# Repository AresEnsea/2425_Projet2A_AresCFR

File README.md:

# 2425_AresCFR
Ce repository contient le travail de l'association Arès dans le cadre de la Coupe de France de Robotique 2024-2025. Il contient tous les fichiers CAO, Kicad, Python, C ainsi que les photos, diagrammes et schémas qui ont fait avancer le projet.

## Répartition
Dépôt du projet de coupe de France de robotique 2024/2025
- 1A : Ce repository contient le travail des 1ères années membres de l'association Arès à l'ENSEA sur les PAMIs de la Coupe de France de Robotique

Read me 1A :
      https://github.com/AresEnsea/2425_Projet2A_AresCFR/blob/main/1A/README.md
      
- 2A : Ce repository contient le travail des 2èmes années membres de l'association Arès à l'ENSEA sur le robot principal de la Coupe de France de Robotique

Read me 2A :
      https://github.com/AresEnsea/2425_Projet2A_AresCFR/blob/main/2A/README.md

https://github.com/user-attachments/assets/8da76ca9-4337-4687-90c1-276035e22721

## Règlement
Le but de la compétition est de faire réaliser des actions de différentes difficultés grâce à des robots complétement autonomes, en lien avec le thème de l'année. Cette année le robot principal devra pouvoir se déplacer, déplacer des cannettes et des planches en bois de sorte à les empiler selon l'ordre suivant (2 canettes - 1 planche, 2 canettes - 1 planche , 2 canettes - 1 planche) pour un maximum de 3 étages, chaque étage rapporte plus de points que le précédent, le tout pour atteindre le score le plus grand. Cette année les PAMIs (Petits Actionneur Motorisés Indépendants) censés aider le robot principal en rapportant également des points sont d'une grande importance puisque rapporte en théorie autant de points qiue le robot principal, ils réaliseront des actions simples (déplacement et activation d'un actionneurs), un se distingue parmi eux le "Superstar" qui devra grimper sur l'estrade de la table et se rapprocher le plus du bord sans tomber pour gagner des points.

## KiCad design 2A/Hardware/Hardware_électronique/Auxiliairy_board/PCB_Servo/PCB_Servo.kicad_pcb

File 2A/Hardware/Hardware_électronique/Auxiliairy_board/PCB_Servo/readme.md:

# PCB_Servo

## Description :
- Carte servant d'intermédiaire entre la mainboard et tous les servos du robot

## Caractéristiques techniques :
- Le connecteur JST 4 pins recoit la puissance et une information UART de la carte mainboard
- La puissance est convertie en 7.4V pour alimenter les servos
- Le 7.4V est convertie en 3.3V pour alimenter le microprocesseur STM32G071CBUx
- L'information UART est traduite par le microprocesseur en un signal PWM par servo

# Issues
- le modèle de servo moteur devant etre utilisé à changé après avoir finis le routage, il a fallu alors reprendre le routage de toute la puissance de la carte

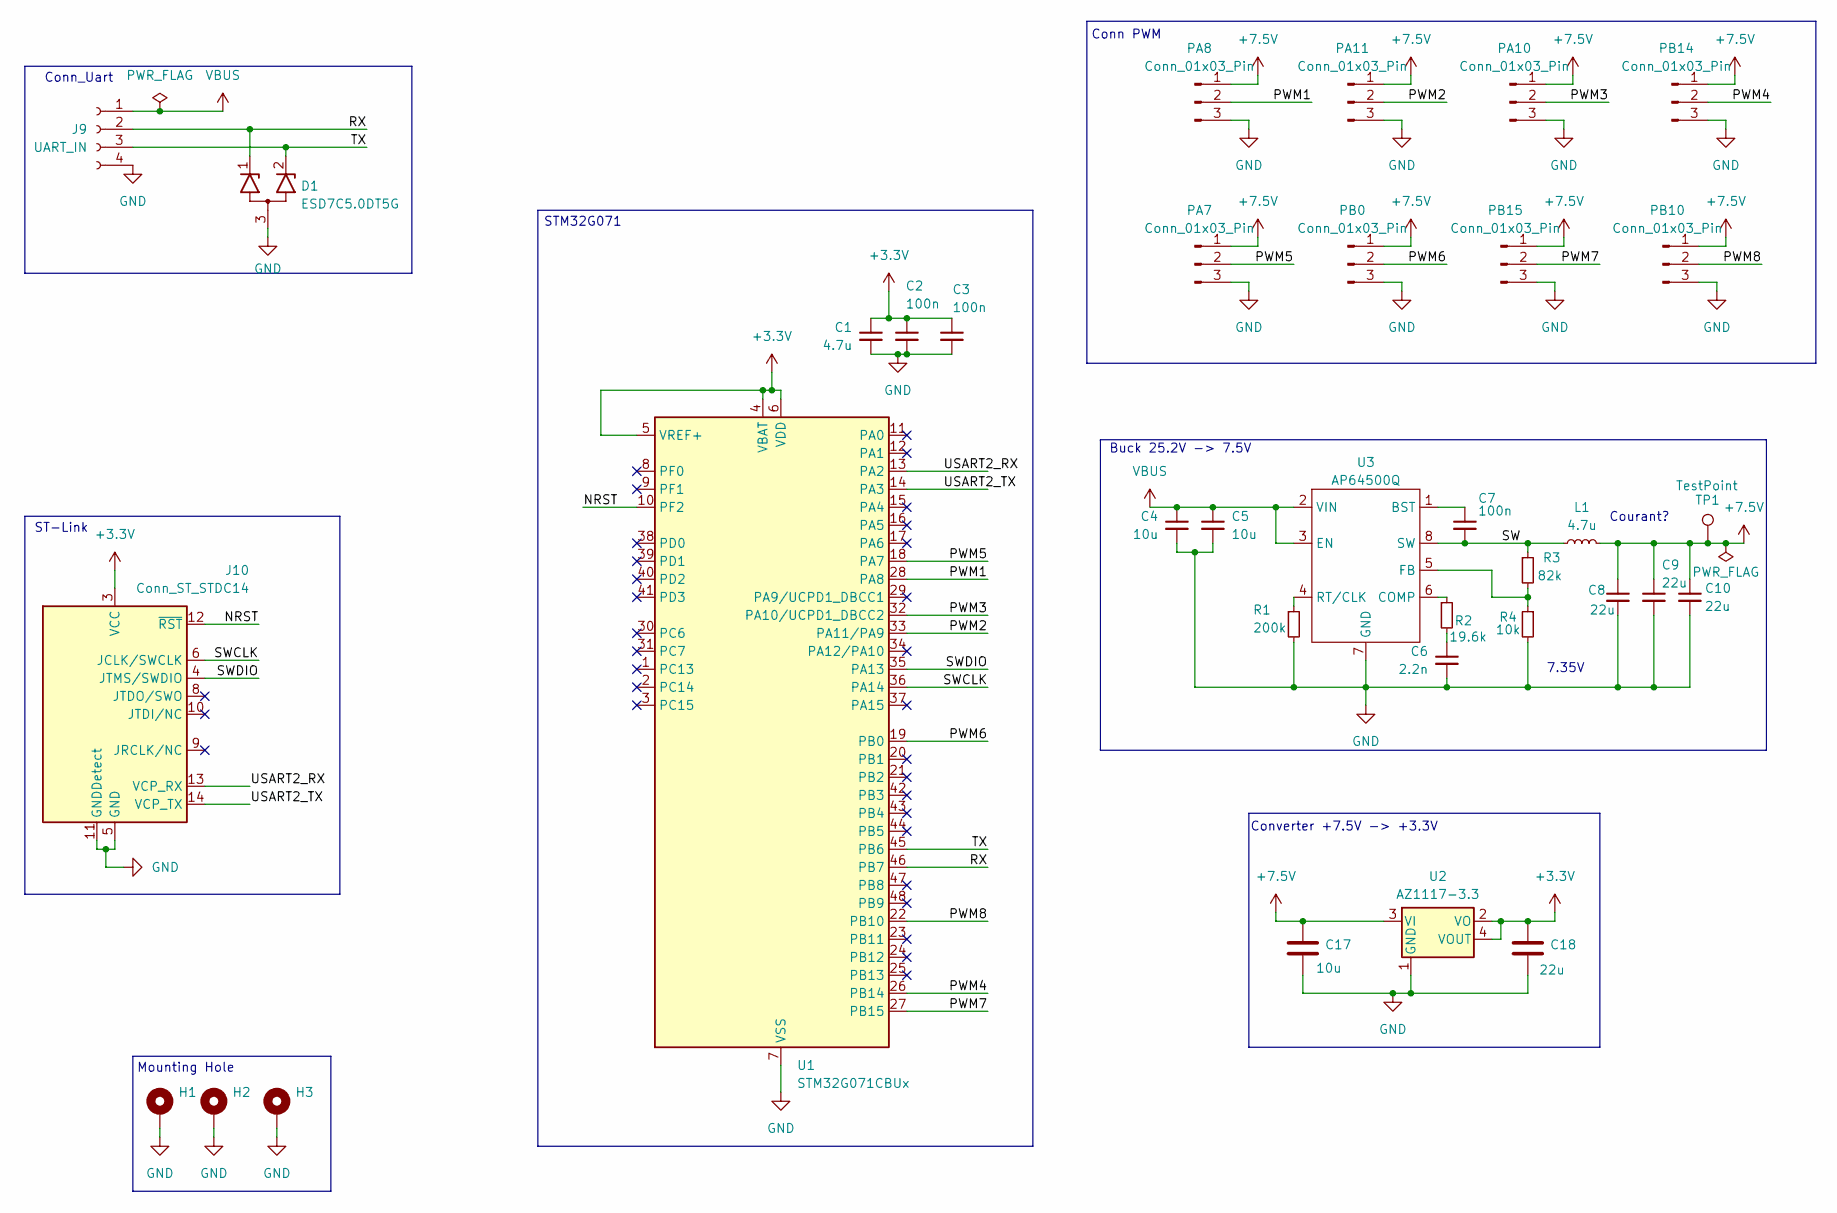
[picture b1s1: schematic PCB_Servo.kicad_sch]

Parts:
C1: 4.7u; C_0402_1005Metric
C2, C3, C7: 100n; C_0402_1005Metric
C4, C5: 10u; C_0805_2012Metric
C6: 2.2n; C_0402_1005Metric
C8, C9, C10: 22u; C_0805_2012Metric
C17: 10u; C_0805_2012Metric_Pad1.18x1.45mm_HandSolder
C18: 22u; C_0805_2012Metric_Pad1.18x1.45mm_HandSolder
D1: ESD7C5.0DT5G; SOT-416; Mouser Part Number 863-ESD7C5.0DT5G
H1, H2, H3: MountingHole_Pad; MountingHole_2.7mm_M2.5_Pad
J9: UART_IN; JST_EH_B4B-EH-A_1x04_P2.50mm_Vertical
J10: Conn_ST_STDC14; PinHeader_2x07_P1.27mm_Vertical_SMD
L1: 4.7u; PA5432.472NLT; MPN 74404084220
PA7, PA8, PA10, PA11: Conn_01x03_Pin; JST_EH_B3B-EH-A_1x03_P2.50mm_Vertical
PB0, PB10, PB14, PB15: Conn_01x03_Pin; JST_EH_B3B-EH-A_1x03_P2.50mm_Vertical
R1: 200k; R_0402_1005Metric
R2: 19.6k; R_0402_1005Metric
R3: 82k; R_0402_1005Metric
R4: 10k; R_0402_1005Metric
TP1: TestPoint; TestPoint_Pad_D2.0mm
U1: STM32G071CBUx; QFN-48-1EP_7x7mm_P0.5mm_EP5.6x5.6mm
U2: AZ1117-3.3; SOT-223
U3: AP64500Q; SOIC-8-1EP_3.9x4.9mm_P1.27mm_EP2.95x4.9mm_Mask2.71x3.4mm

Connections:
+3.3V: C1.1, C2.1, C3.1, C18.1, J10.3 (VCC), U1.4 (VBAT), U1.5 (VREF+), U1.6 (VDD), U2.2 (VO), U2.4 (VOUT)
+7.5V: C8.1, C9.1, C10.1, C17.1, L1.2, PA7.1, PA8.1, PA10.1, PA11.1, PB0.1, PB10.1, PB14.1, PB15.1, TP1.1, U2.3 (VI)
/NRST: J10.12 (~RST), U1.10 (PF2)
/PWM1: PA8.2, U1.28 (PA8)
/PWM2: PA11.2, U1.33 (PA11/PA9)
/PWM3: PA10.2, U1.32 (PA10/UCPD1_DBCC2)
/PWM4: PB14.2, U1.26 (PB14)
/PWM5: PA7.2, U1.18 (PA7)
/PWM6: PB0.2, U1.19 (PB0)
/PWM7: PB15.2, U1.27 (PB15)
/PWM8: PB10.2, U1.22 (PB10)
/RX: D1.1 (K1), J9.2, U1.46 (PB7)
/SW: C7.2, L1.1, R3.1, U3.8 (SW)
/SWCLK: J10.6 (JCLK/SWCLK), U1.36 (PA14)
/SWDIO: J10.4 (JTMS/SWDIO), U1.35 (PA13)
/TX: D1.2 (K2), J9.3, U1.45 (PB6)
/USART2_RX: J10.13 (VCP_RX), U1.13 (PA2)
/USART2_TX: J10.14 (VCP_TX), U1.14 (PA3)
GND: C1.2, C2.2, C3.2, C4.2, C5.2, C6.2, C8.2, C9.2, C10.2, C17.2, C18.2, D1.3 (A), H1.1, H2.1, H3.1, J9.4, J10.5 (GND), J10.7 (GND), J10.11 (GNDDetect), PA7.3, PA8.3, PA10.3, PA11.3, PB0.3, PB10.3, PB14.3, PB15.3, R1.2, R4.2, U1.7 (VSS), U1.49 (VSS), U2.1 (GND), U3.7 (GND), U3.9 (EPad)
unnamed: C6.1, R2.2
unnamed: C7.1, U3.1 (BST)
unnamed: R2.1, U3.6 (COMP)
unnamed: R3.2, R4.1, U3.5 (FB)
unnamed: R1.1, U3.4 (RT/CLK)
VBUS: C4.1, C5.1, J9.1, U3.2 (VIN), U3.3 (EN)

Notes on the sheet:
Converter +7.5V -> +3.3V
Mounting Hole
Buck 25.2V -> 7.5V
7.35V
Courant?
Conn_Uart
STM32G071
ST-Link
Conn PWM

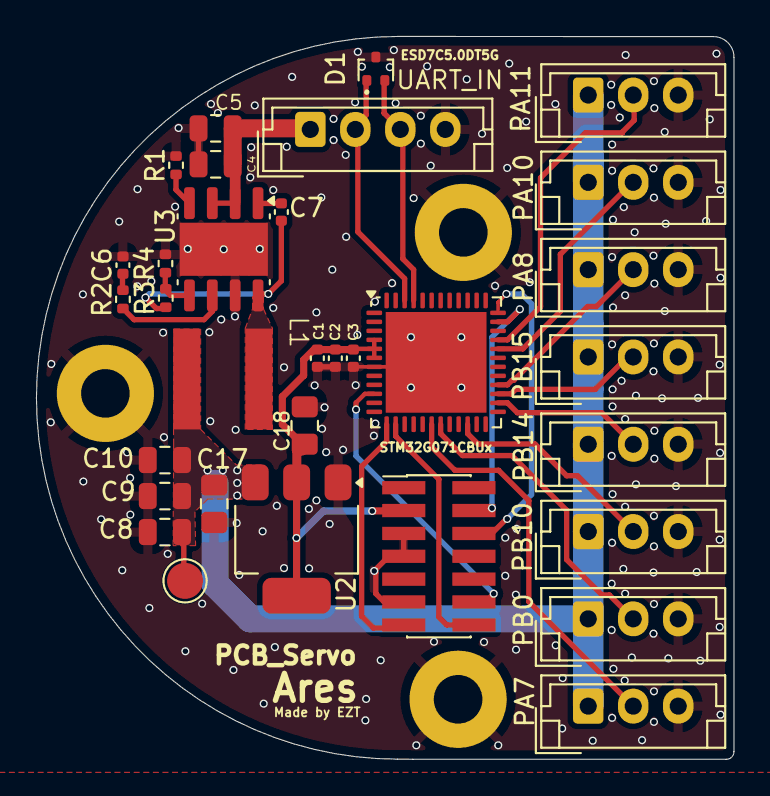
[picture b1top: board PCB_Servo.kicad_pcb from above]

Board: 2 copper layers, 38.8 x 40.2 mm, 35 parts (0 on the bottom side), 25 nets.

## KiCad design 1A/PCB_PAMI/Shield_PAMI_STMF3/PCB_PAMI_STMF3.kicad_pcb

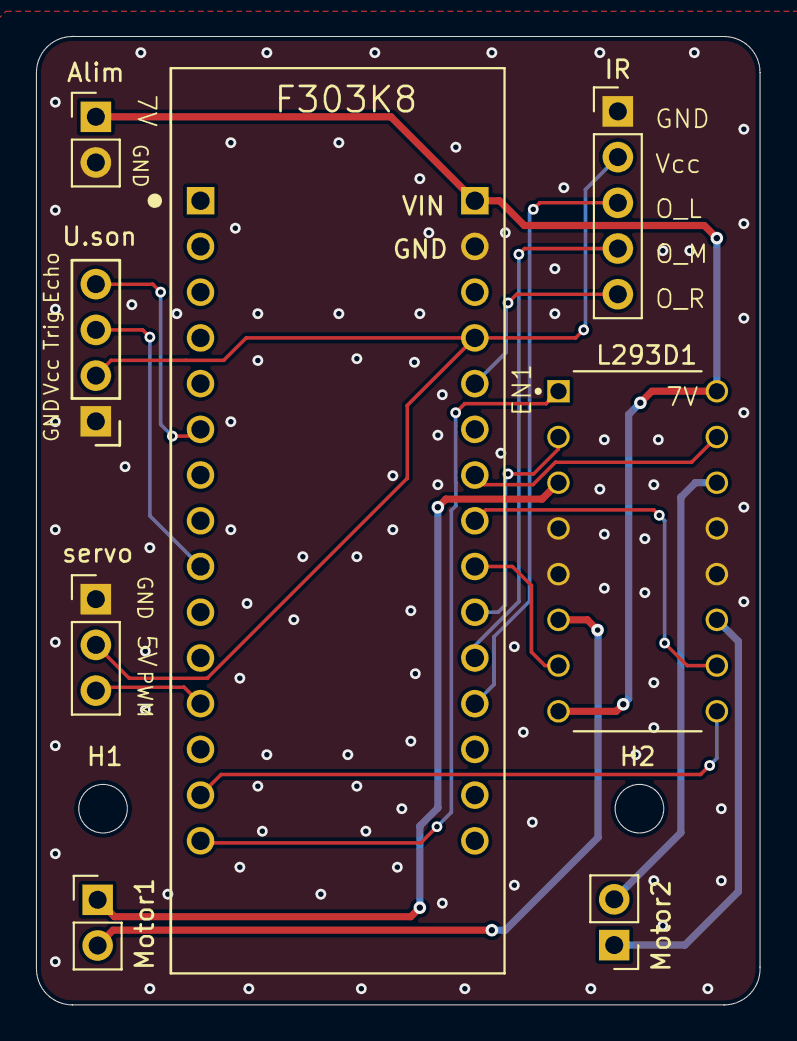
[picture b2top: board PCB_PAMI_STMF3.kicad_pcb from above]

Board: 2 copper layers, 40.2 x 53.8 mm, 10 parts (0 on the bottom side), 19 nets.

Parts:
Alim: PinHeader_1x02_P2.54mm_Vertical
F303K8: MODULE_NUCLEO-F303K8
H1, H2: MountingHole_Pad; MountingHole_2.7mm_M2.5
IR: PinHeader_1x05_P2.54mm_Vertical
L293D1: L293D; L293D_Motor_Driver
Motor1, Motor2: PinHeader_1x02_P2.54mm_Vertical
U.son: PinHeader_1x04_P2.54mm_Vertical
servo: PinHeader_1x03_P2.54mm_Vertical

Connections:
/5V: F303K8.4_4 (5V), IR.2 (VCC), U.son.2 (Vcc), servo.1 (GND)
/7V: Alim.1 (7V), F303K8.4_1 (VIN), L293D1.8 (VS), L293D1.16 (VSS)
/EN1: F303K8.3_15 (PB_4), L293D1.1 (ENABLE1)
/EN2: F303K8.3_14 (PB_5), L293D1.9 (ENABLE2)
/Echo: F303K8.3_6 (PB_0), U.son.4 (Echo)
/GND: Alim.2 (GND), F303K8.4_2 (GND), IR.1 (GND), L293D1.4 (GND), L293D1.5 (GND), L293D1.12 (GND), L293D1.13 (GND), U.son.1 (GND), servo.2 (5V)
/IN1: F303K8.4_10 (PA_3), L293D1.2 (INPUT1)
/IN2: F303K8.4_9 (PA_4), L293D1.7 (INPUT2)
/IN3: F303K8.4_8 (PA_5), L293D1.10 (INPUT3)
/IN4: F303K8.4_7 (PA_6), L293D1.15 (INPUT4)
/O_L: F303K8.4_12 (PA_0), IR.3 (O_L)
/O_M: F303K8.4_11 (PA_1), IR.4 (O_M)
/O_R: F303K8.4_5 (PA_2), IR.5 (O_R)
/Trig: F303K8.3_9 (PB_1), U.son.3 (Trig)
/out1: L293D1.3 (OUTPUT1), Motor1.1 (input1)
/out2: L293D1.6 (OUTPUT2), Motor1.2 (input2)
/out3: L293D1.11 (OUTPUT3), Motor2.1 (input1)
/out4: L293D1.14 (OUTPUT4), Motor2.2 (input2)
/pwm_servo: F303K8.3_12 (PA_8), servo.3 (PWM)

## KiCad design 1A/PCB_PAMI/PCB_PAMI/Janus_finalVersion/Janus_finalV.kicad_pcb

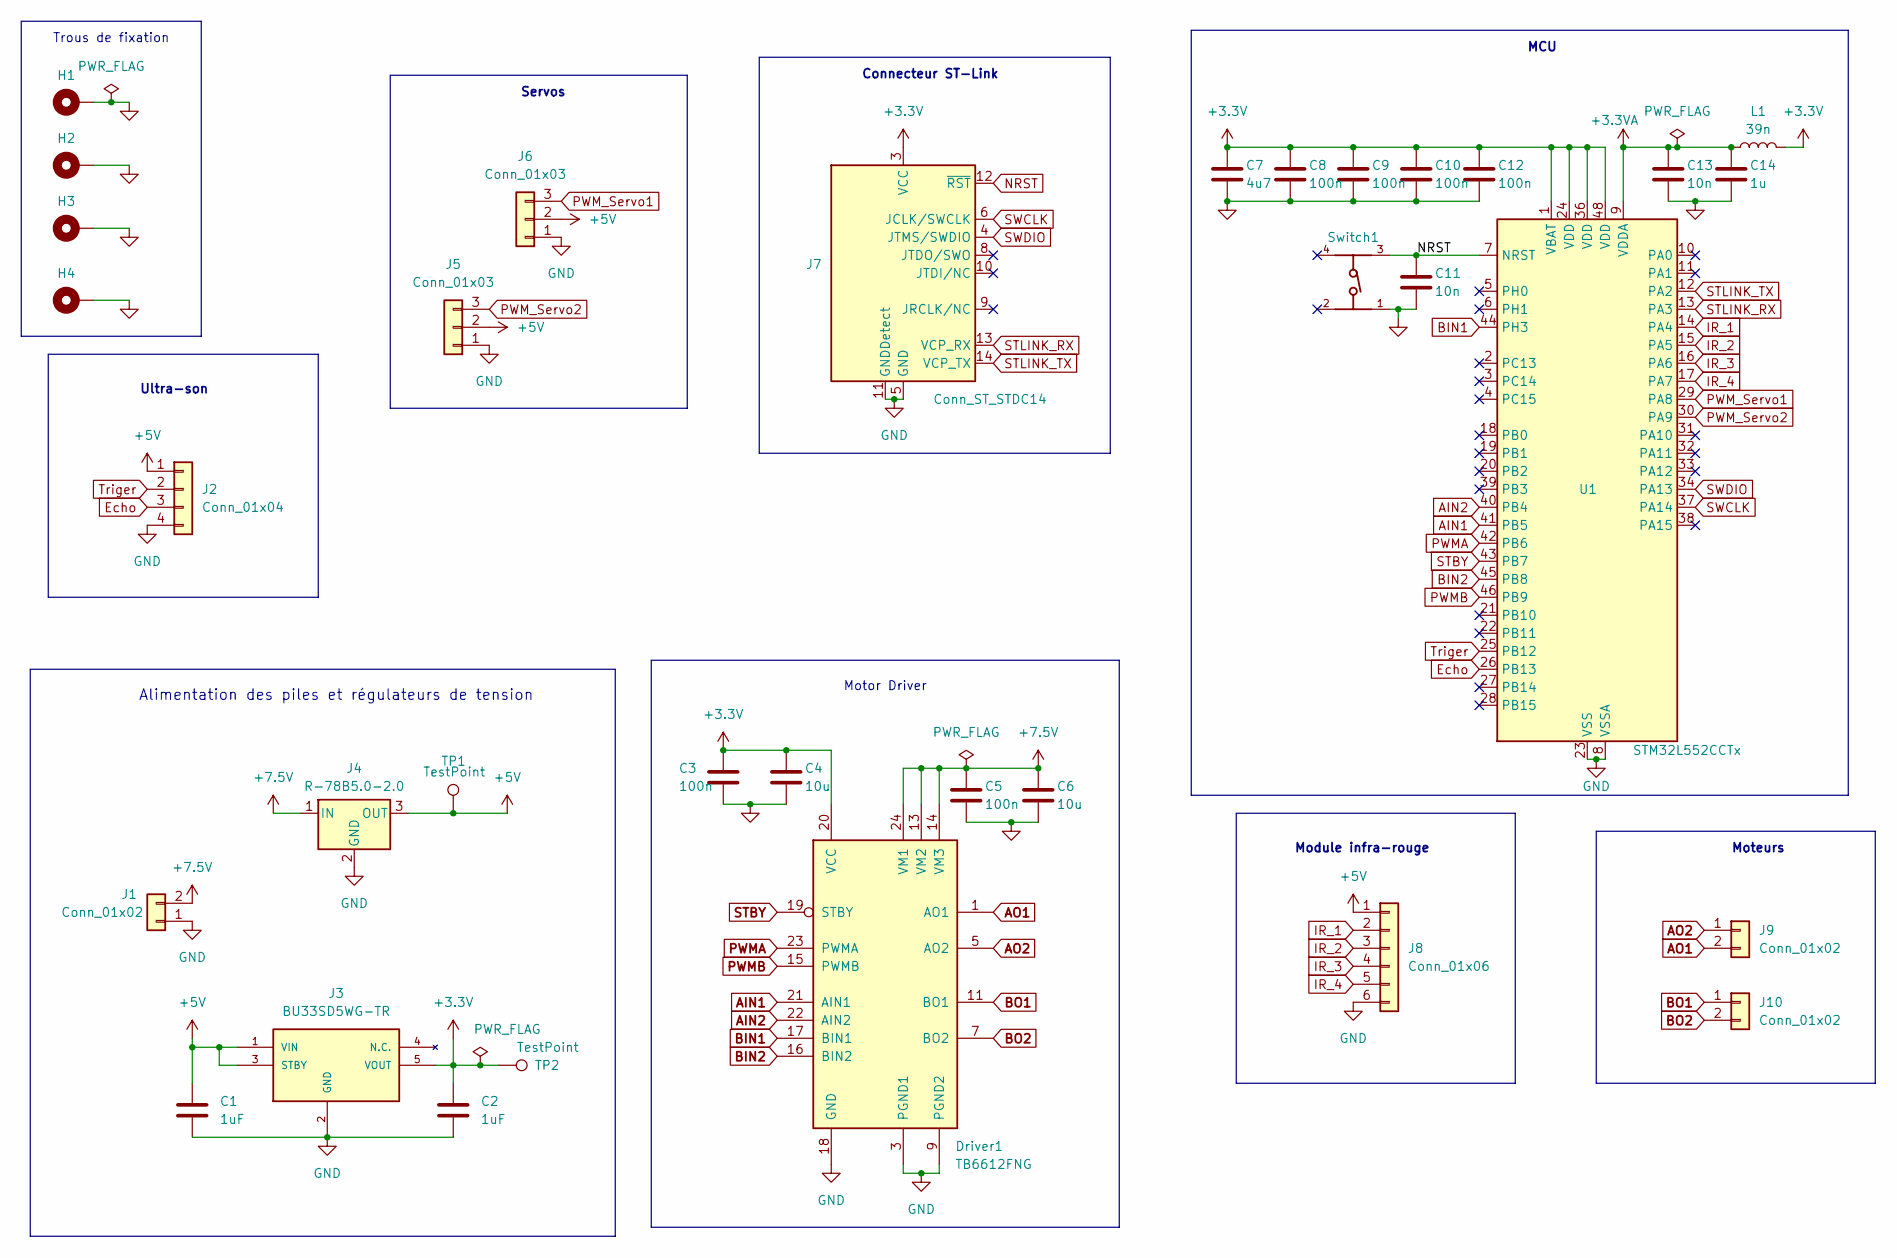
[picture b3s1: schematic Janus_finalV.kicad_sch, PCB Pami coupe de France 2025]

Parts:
C1, C2: 1uF; C_0603_1608Metric_Pad1.08x0.95mm_HandSolder
C3, C5, C8, C9, C10, C12: 100n; C_0402_1005Metric
C4, C6: 10u; C_0805_2012Metric
C7: 4u7; C_0805_2012Metric
C11, C13: 10n; C_0402_1005Metric
C14: 1u; C_0402_1005Metric
Driver1: TB6612FNG; SSOP-24_5.3x8.2mm_P0.65mm
H1, H2, H3, H4: MountingHole_Pad; MountingHole_2.7mm_M2.5_Pad
J1: Conn_01x02; JST_XH_S2B-XH-A-1_1x02_P2.50mm_Horizontal
J2: Conn_01x04; JST_PH_B4B-PH-K_1x04_P2.00mm_Vertical
J3: BU33SD5WG-TR; SOT95P280X125-5N; Mouser_Part_Number 755-BU33SD5WG-TR
J4: R-78B5.0-2.0; Converter_DCDC_RECOM_R-78B-2.0_THT
J5, J6: Conn_01x03; JST_XH_B3B-XH-A_1x03_P2.50mm_Vertical
J7: Conn_ST_STDC14; PinHeader_2x07_P1.27mm_Vertical_SMD
J8: Conn_01x06; JST_XH_S6B-XH-A-1_1x06_P2.50mm_Horizontal
J9, J10: Conn_01x02; JST_XH_B2B-XH-A_1x02_P2.50mm_Vertical
L1: 39n; L_0603_1608Metric
Switch1: 430471025826; PART-NUMBER 430471025826
TP1, TP2: TestPoint; TestPoint_Pad_D2.0mm
U1: STM32L552CCTx; LQFP-48_7x7mm_P0.5mm

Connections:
+3.3V: C2.1, C3.1, C4.1, C7.1, C8.1, C9.1, C10.1, C12.1, Driver1.20 (VCC), J3.5 (VOUT), J7.3 (VCC), L1.2, TP2.1, U1.1 (VBAT), U1.24 (VDD), U1.36 (VDD), U1.48 (VDD)
+3.3VA: C13.1, C14.1, L1.1, U1.9 (VDDA)
+5V: C1.1, J2.1, J3.1 (VIN), J3.3 (STBY), J4.3 (OUT), J5.2, J6.2, J8.1, TP1.1
+7.5V: C5.1, C6.1, Driver1.13 (VM2), Driver1.14 (VM3), Driver1.24 (VM1), J1.2, J4.1 (IN)
AIN1: Driver1.21 (AIN1), U1.41 (PB5)
AIN2: Driver1.22 (AIN2), U1.40 (PB4)
AO1: Driver1.1 (AO1), Driver1.2 (AO1), J9.2
AO2: Driver1.5 (AO2), Driver1.6 (AO2), J9.1
BIN1: Driver1.17 (BIN1), U1.44 (PH3)
BIN2: Driver1.16 (BIN2), U1.45 (PB8)
BO1: Driver1.11 (BO1), Driver1.12 (BO1), J10.1
BO2: Driver1.7 (BO2), Driver1.8 (BO2), J10.2
Echo: J2.3, U1.26 (PB13)
GND: C1.2, C2.2, C3.2, C4.2, C5.2, C6.2, C7.2, C8.2, C9.2, C10.2, C11.2, C12.2, C13.2, C14.2, Driver1.3 (PGND1), Driver1.4 (PGND1), Driver1.9 (PGND2), Driver1.10 (PGND2), Driver1.18 (GND), H1.1, H2.1, H3.1, H4.1, J1.1, J2.4, J3.2 (GND), J4.2 (GND), J5.1, J6.1, J7.5 (GND), J7.7 (GND), J7.11 (GNDDetect), J8.6, Switch1.1, U1.8 (VSSA), U1.23 (VSS), U1.35 (VSS), U1.47 (VSS)
IR_1: J8.2, U1.14 (PA4)
IR_2: J8.3, U1.15 (PA5)
IR_3: J8.4, U1.16 (PA6)
IR_4: J8.5, U1.17 (PA7)
NRST: C11.1, J7.12 (~RST), Switch1.3, U1.7 (NRST)
PWMA: Driver1.23 (PWMA), U1.42 (PB6)
PWMB: Driver1.15 (PWMB), U1.46 (PB9)
PWM_Servo1: J6.3, U1.29 (PA8)
PWM_Servo2: J5.3, U1.30 (PA9)
STBY: Driver1.19 (STBY), U1.43 (PB7)
STLINK_RX: J7.13 (VCP_RX), U1.13 (PA3)
STLINK_TX: J7.14 (VCP_TX), U1.12 (PA2)
SWCLK: J7.6 (JCLK/SWCLK), U1.37 (PA14)
SWDIO: J7.4 (JTMS/SWDIO), U1.34 (PA13)
Triger: J2.2, U1.25 (PB12)

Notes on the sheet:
Trous de fixation
Servos
Moteurs
Module infra-rouge
Connecteur ST-Link
Ultra-son
Alimentation des piles et régulateurs de tension
Motor Driver
MCU

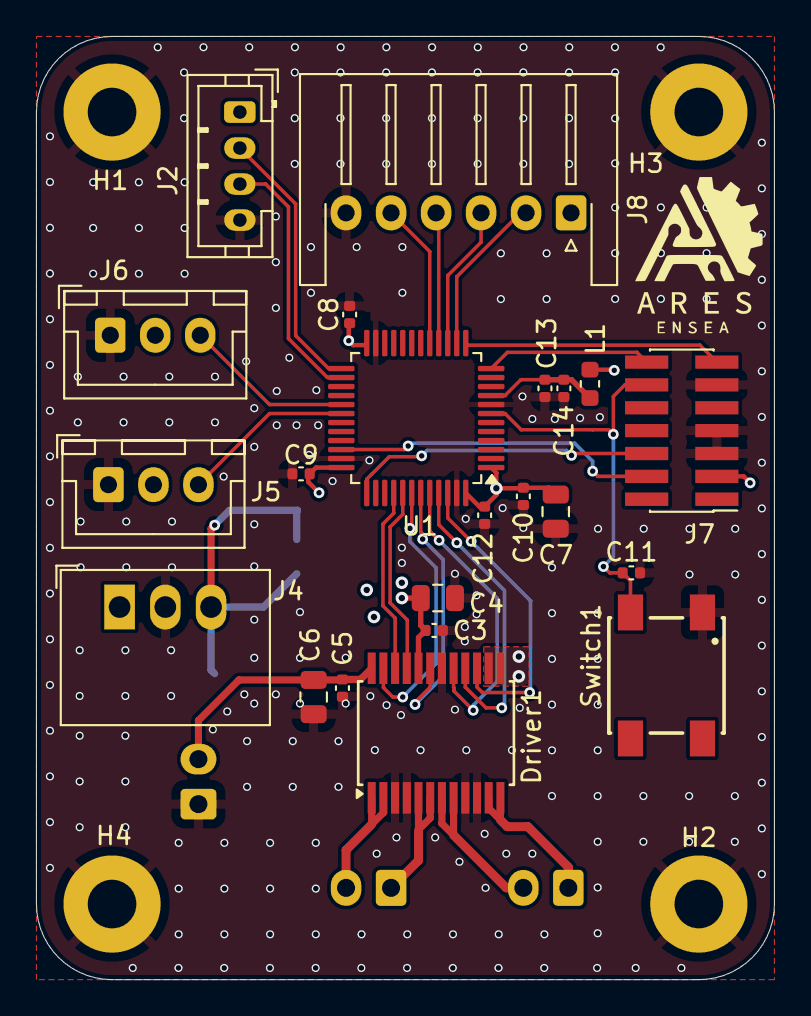
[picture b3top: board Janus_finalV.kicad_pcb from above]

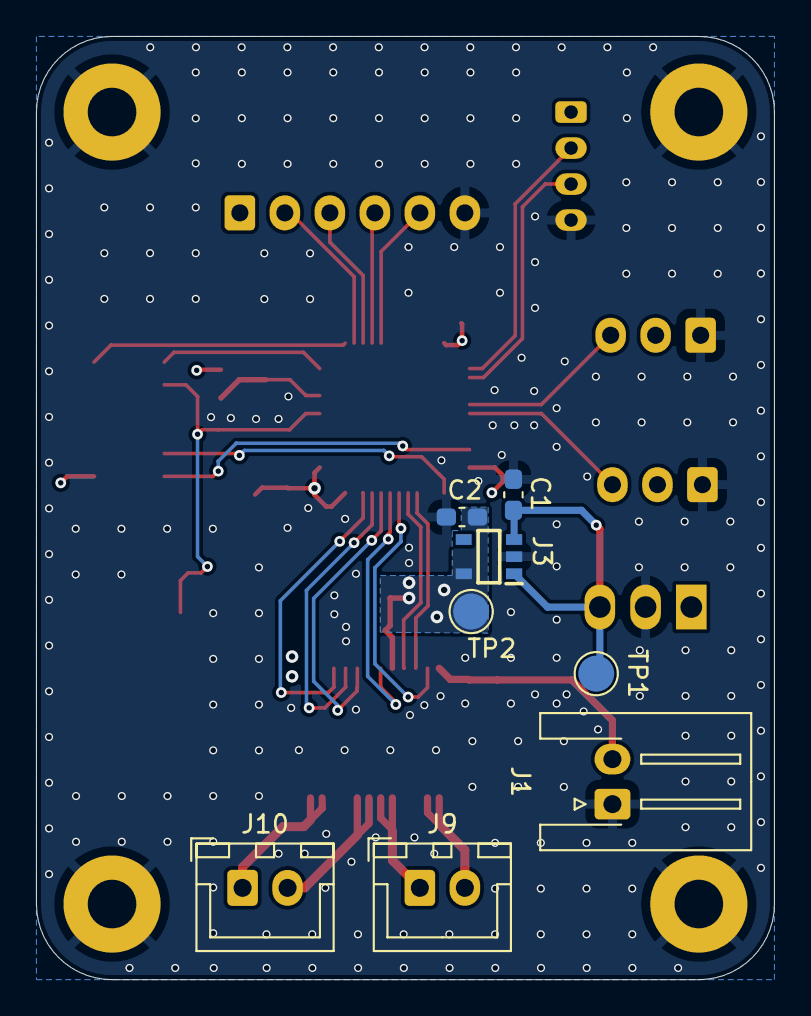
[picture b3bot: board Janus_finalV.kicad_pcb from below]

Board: 4 copper layers, 41.0 x 52.4 mm, 34 parts (8 on the bottom side), 29 nets.

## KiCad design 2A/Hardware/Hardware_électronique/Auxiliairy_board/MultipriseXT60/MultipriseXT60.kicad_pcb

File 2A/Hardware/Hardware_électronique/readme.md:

# Rapport de fin de semestre :

Durant ce semestre notre équipe à pu réaliser différents PCB...

## PCB_ MotherBoard

### Description : 
 - La carte mère permet l'alimentation et la laison des péripériques (capteurs, actionneurs...) 
au microcontrolleur (STM32H735) les commandants et permet également à la stm32 de communiquer
avec un raspberry pi qui ferait du traitement d'information ainsi que la communication vers l'extérieur 
via le WIFI.

### Features Principales: 
 - 9 liasons inter cartes : connecteur JST4 (1 UART + alimentation 24V).
 - Shield pour Raspberry Pi assurant l'alimentation 5V ainsi qu'une liason UART.

### Issues :
 - Malheuresement, suite à une erreur d'empreinte, le PCBMotherBoard 

## PCB_Moteur V3

### Descriptopn :
 - Carte de pilotage des moteurs de la base roulante. Nous avons prévu une carte par moteur.

### Caractéristiques techniques : 
- Supporter les appels de courants jusqu'à 10A par moteur.
- Connction des sondes à effet hall du moteur en RS323.
- Connection du moteur en XT30.
- STM32G474 embarquée pour communiquer avec la carte mère ainsi que les différents péripériques de la carte.
- Capteur de Température.
- Sondes à effet Hall pour la mesure de courant instantané consommé par le moteur.
- Possibilté de brancher un ventilateur.
  
### Issues :

-  La V1 du PCB n'a pas été concluante suite au non fonctionnement d'un convertisseur buck. Celui-ci à été changé dans la V2.
-  La V2 à fonctionné mais avec un problème qui faisairt que le moteur ne touranit que dans un sens. La V3 rajoute une resistance de sense entre le bras de pont et le mosfet driver. 

## PCB_Stepper 

### Description :
 - Carte de pilotage pour 2 steppers steppers.

### Caractéristiques principales : 
 - Supporte l'eau la plie les pets et le vent grâce aux 2 TMC2225 embarqué pour le pilotage des steppers.
 - STM32G071 embarquée pour la liason UART avec la carte mère ainsi que la commande des moteurs...

### Issues :

- V1 actuelle .
- Pour la V2 ce serait bien de mesure de courant en instantané.

# PCB_Servo

## Description :
- Carte servant d'intermédiaire entre la mainboard et tous les servos du robot

## Caractéristiques techniques :
- Le connecteur JST 4 pins recoit la puissance et une information UART de la carte mainboard.
- La puissance est convertie de 25.2V en 7.4V pour alimenter les servos.
- Le 7.4V est convertie en 3.3V pour alimenter le microprocesseur STM32G071CBUx.
- L'information UART est traduite par le microprocesseur en un signal PWM par servo.

## Finalité:
Quatre PCB servos furent soudés. 
Trois sont opérationnels, cela nous permet d'en avoir deux dans le robot et un en réserve par sécurité.
En effet, un PCB servo peut commander 8 servos et il y a 12 servos à commander à la fois sur le robot.
Le troisième constitue une sécurité au cas ou une des deux cartes utilisées viendrait à casser (court-circuit, surcharge, choque...).

# Issues
- Le modèle de servo moteur devant etre utilisé à changé après avoir finis le routage, il a fallu alors reprendre le routage de toute la puissance de la carte
- Sur les quatre PCB soudés, tous ne fonctionnent pas parfaitement:
   Je ne suis pas parvenu à téléverser un quelconque programme sur le microprocesseur de la première carte que j'ai soudé. Celle-ci est donc considéré comme HS.
   La deuxième carte est opérationnelle mais je lui ai relevé deux défaults. Premièrement, elle délivre du 8,2V aux servos au lieu de 7,6V. Deuxièmement, je n'ai réussis qu'à souder 6 connecteurs JST pour relier la carte aux servos.
   Les deux cartes soudées en dernières fonctionnent parfaitement (aucun problème de fonctionnement relevé).
  
# Schéma Final du Hardware
En suivant ce lien vous trouverez un schéma de tous les PCB ci-dessus avec câblage entre eux :

https://lucid.app/lucidspark/aabfef21-1fd2-40bf-9924-298b6e461ffa/view

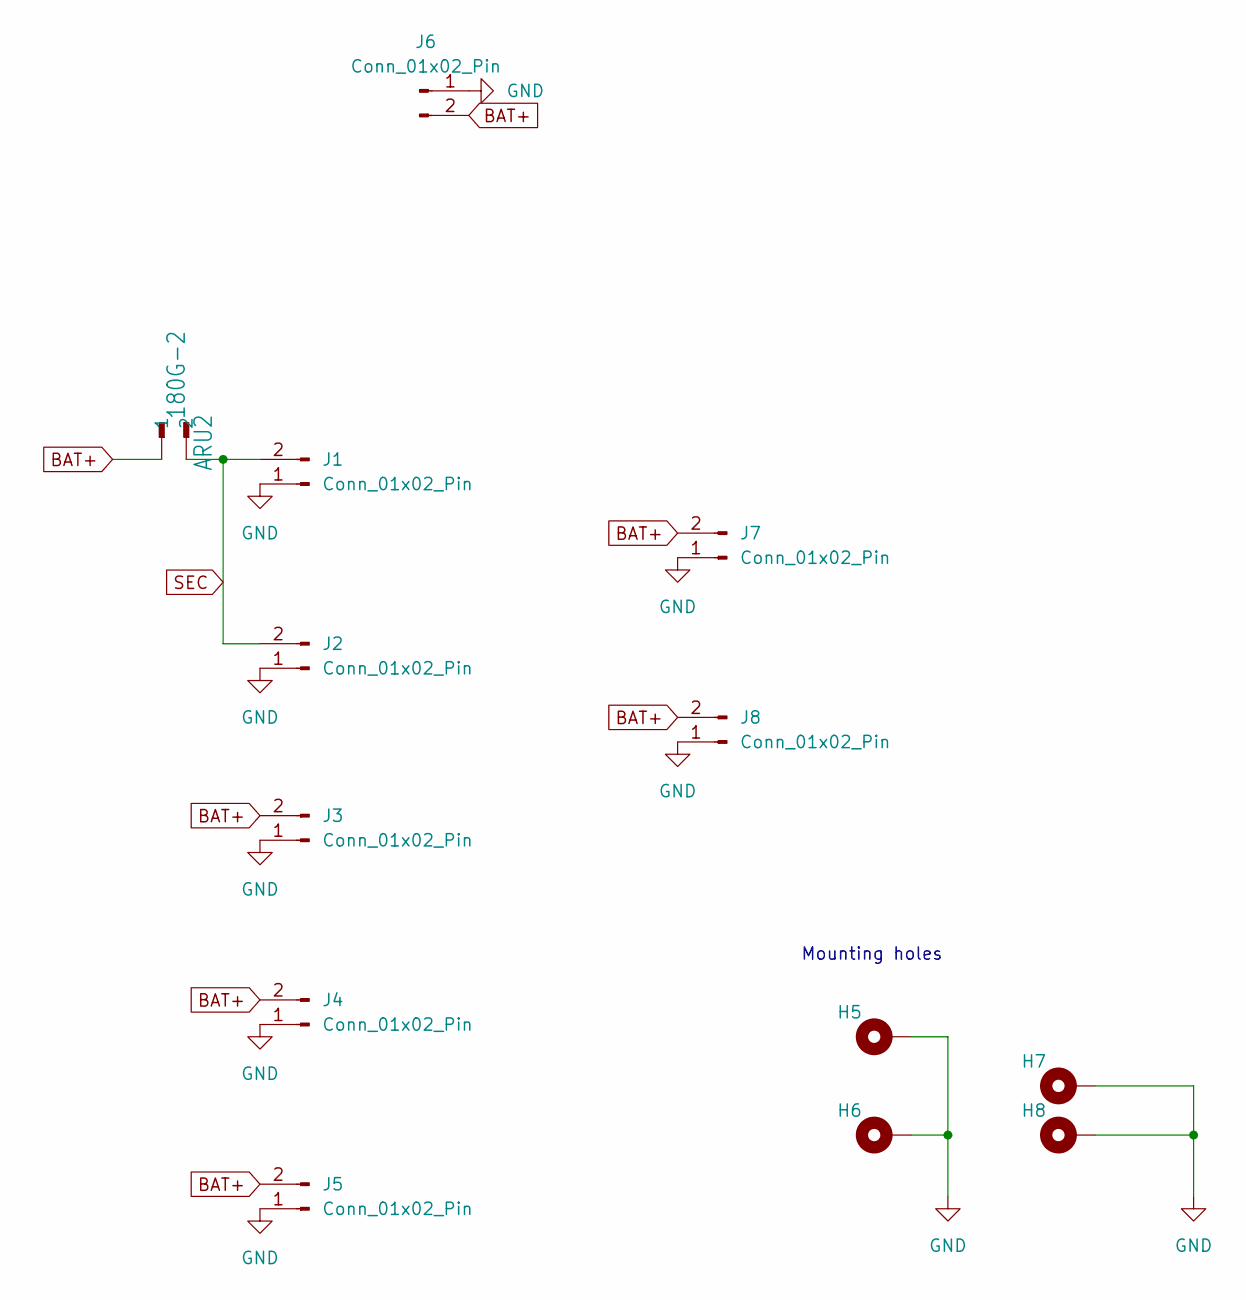
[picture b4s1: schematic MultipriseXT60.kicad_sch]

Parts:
ARU2: 180G-2; AMASS_XT60-F_1x02_P7.20mm_Vertical
H5, H6, H7, H8: MountingHole_Pad; MountingHole_3.2mm_M3_Pad_Via
J1, J2, J3, J4, J5, J6, J7, J8: Conn_01x02_Pin; AMASS_XT60-F_1x02_P7.20mm_Vertical

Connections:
BAT+: ARU2.1, J3.2, J4.2, J5.2, J6.2, J7.2, J8.2
GND: H5.1, H6.1, H7.1, H8.1, J1.1, J2.1, J3.1, J4.1, J5.1, J6.1, J7.1, J8.1
SEC: ARU2.2, J1.2, J2.2

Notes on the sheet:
Mounting holes

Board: 2 copper layers, 13 parts (0 on the bottom side), 3 nets, no tracks yet.

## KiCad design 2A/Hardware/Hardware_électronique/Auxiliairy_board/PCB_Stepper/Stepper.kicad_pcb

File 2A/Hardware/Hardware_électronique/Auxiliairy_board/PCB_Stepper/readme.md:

# PCB_Stepper 

## Description :
 - Carte de pilotage pour 2 steppers steppers.

## Caractéristiques principales : 
 - Supporte l'eau la plie les pets et le vent grâce aux 2 TMC2225 embarqué pour le pilotage des steppers.
 - STM32G071 embarquée pour la liason UART avec la carte mère ainsi que la commande des moteurs...

## Issues :

- V1 actuelle .
- Pour la V2 ce serait bien de mesure de courant en instantané.

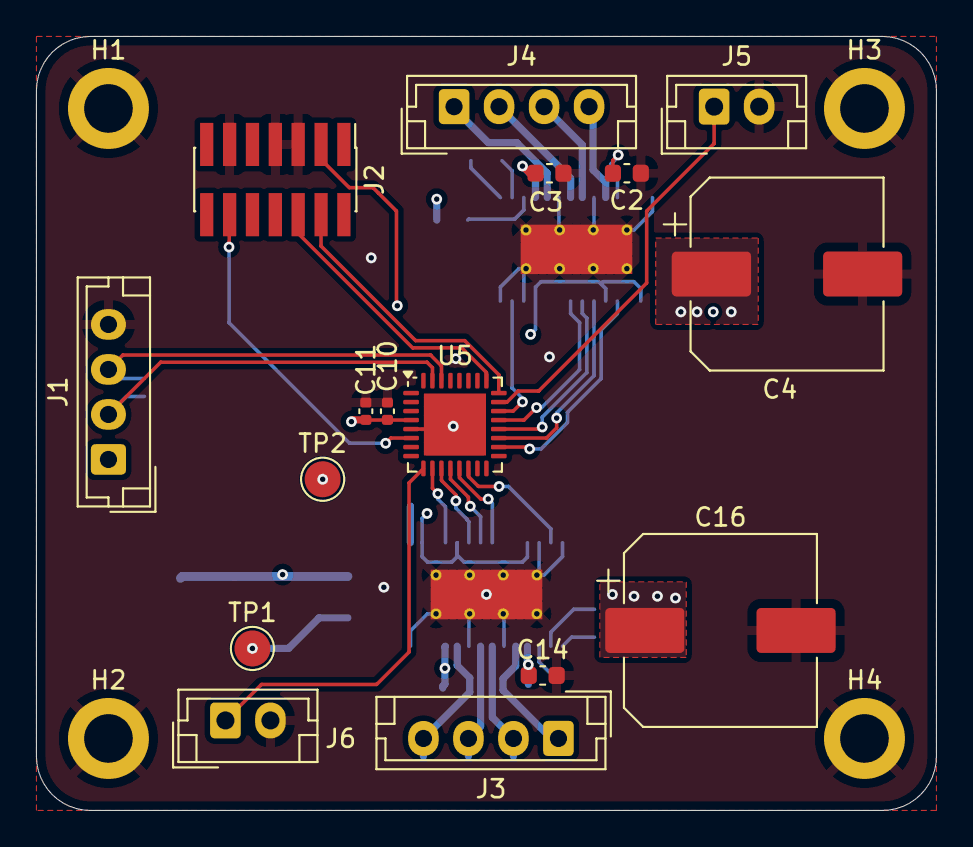
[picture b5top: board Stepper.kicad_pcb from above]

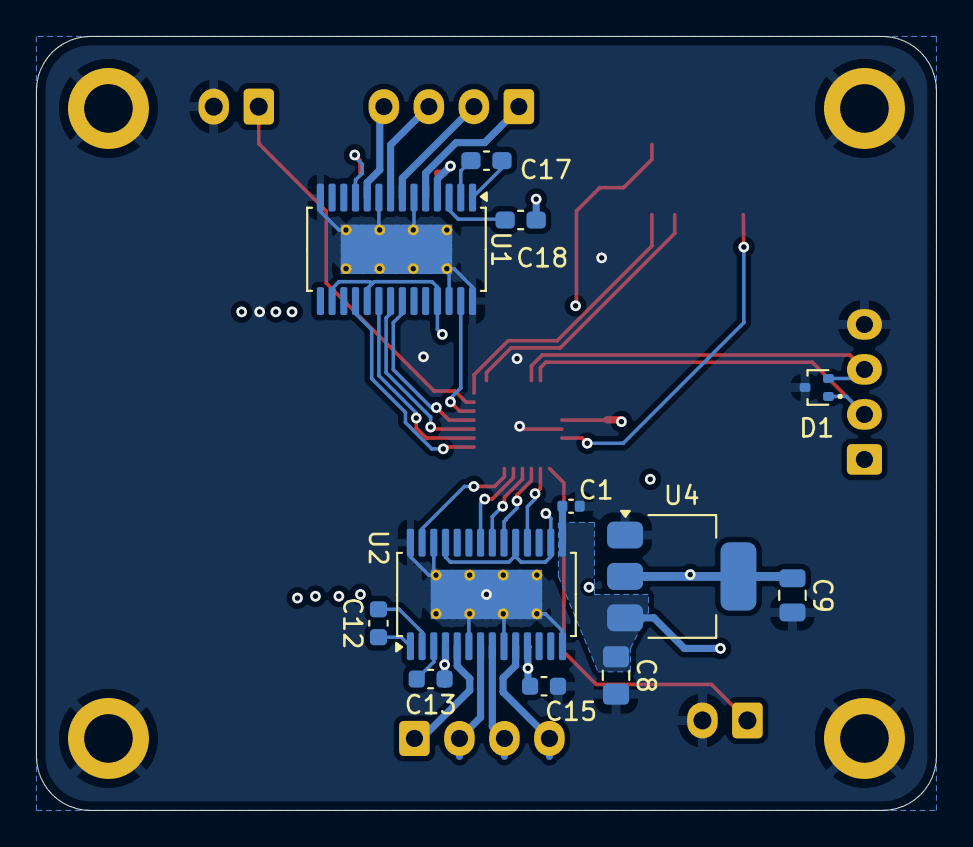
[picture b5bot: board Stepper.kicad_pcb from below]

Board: 4 copper layers, 50.0 x 43.0 mm, 32 parts (12 on the bottom side), 35 nets.

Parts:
C1: 2u2; C_0402_1005Metric
C2, C3, C13, C14, C15: 100n; C_0603_1608Metric
C4, C16: 100u; CP_Elec_10x10.5
C8: 10u; C_0805_2012Metric_Pad1.18x1.45mm_HandSolder
C9: 22u; C_0805_2012Metric
C10: 100n; C_0402_1005Metric
C11: 4.7u; C_0402_1005Metric
C12: 22n; C_0603_1608Metric
C17: 22n; C_0603_1608Metric_Pad1.08x0.95mm_HandSolder
C18: 100n; C_0603_1608Metric_Pad1.08x0.95mm_HandSolder
D1: ESD7C5.0DT5G; SOT-416
H1, H2, H3, H4: MountingHole_Pad; MountingHole_2.7mm_M2.5_ISO7380_Pad
J1: UART_IN; JST_EH_B4B-EH-A_1x04_P2.50mm_Vertical
J2: Conn_ST_STDC14; PinHeader_2x07_P1.27mm_Vertical_SMD
J3, J4: Conn_01x04; JST_EH_B4B-EH-A_1x04_P2.50mm_Vertical
J5: FinCourse1; JST_EH_B2B-EH-A_1x02_P2.50mm_Vertical
J6: FinCourse2; JST_EH_B2B-EH-A_1x02_P2.50mm_Vertical
TP1: 5V; TestPoint_Pad_D2.0mm
TP2: 3.3V; TestPoint_Pad_D2.0mm
U1, U2: TMC2225; HTSSOP-28-1EP_4.4x9.7mm_P0.65mm_EP2.75x6.2mm_ThermalVias
U4: AZ1117-3.3; SOT-223-3_TabPin2
U5: STM32G071KBUx; QFN-32-1EP_5x5mm_P0.5mm_EP3.45x3.45mm

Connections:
+3.3V: C9.1, C10.1, C11.1, J2.3 (VCC), TP2.1, U1.16 (VCC_IO), U1.19 (SPREAD), U1.25 (MS1_AD0), U2.16 (VCC_IO), U2.19 (SPREAD), U2.25 (MS1_AD0), U4.2 (VO), U5.4 (VDD)
+5V: C1.2, C8.1, TP1.1, U2.15 (5VOUT), U4.3 (VI)
/Course1: J5.1, U5.23 (PA12/PA10)
/Course2: J6.1, U5.9 (PA2)
/DIAG1: U1.18 (DIAG), U5.18 (PA8)
/DIAG2: U2.18 (DIAG), U5.10 (PA3)
/NRST: J2.12 (~RST), U5.6 (PF2)
/RX: D1.1 (K1), J1.2, U5.31 (PB7)
/SWCLK: J2.6 (JCLK/SWCLK), U5.25 (PA14)
/SWDIO: J2.4 (JTMS/SWDIO), U5.24 (PA13)
/TX: D1.2 (K2), J1.3, U5.30 (PB6)
/U1_OA1: J4.2, U1.7 (OA1)
/U1_OA2: J4.1, U1.5 (OA2)
/U1_OB1: J4.3, U1.8 (OB1)
/U1_OB2: J4.4, U1.10 (OB2)
/U2_OA1: J3.2, U2.7 (OA1)
/U2_OA2: J3.1, U2.5 (OA2)
/U2_OB1: J3.3, U2.8 (OB1)
/U2_OB2: J3.4, U2.10 (OB2)
/dir1: U1.20 (DIR), U5.19 (PA9/UCPD1_DBCC1)
/dir2: U2.20 (DIR), U5.11 (PA4)
/index1: U1.27 (INDEX), U5.22 (PA11/PA9)
/index2: U2.27 (INDEX), U5.14 (PA7)
/step1: U1.22 (STEP), U5.21 (PA10/UCPD1_DBCC2)
/step2: U2.22 (STEP), U5.13 (PA6)
/~EN1: U1.21 (~EN), U5.20 (PC6)
/~EN2: U2.21 (~EN), U5.12 (PA5)
GND: C1.1, C2.2, C3.2, C4.2, C8.2, C9.2, C10.2, C11.2, C14.2, C15.2, C16.2, D1.3 (A), H1.1, H2.1, H3.1, H4.1, J1.4, J2.5 (GND), J2.7 (GND), J2.11 (GNDDetect), J5.2, J6.2, U1.6 (BRA), U1.9 (BRB), U1.14 (GND), U1.26 (MS2_AD1), U1.28 (GND), U1.29 (GND), U2.6 (BRA), U2.9 (BRB), U2.14 (GND), U2.26 (MS2_AD1), U2.28 (GND), U2.29 (GND), U4.1 (GND), U5.5 (VSS), U5.33 (VSS)
unnamed: C17.2, U1.2 (CPI)
unnamed: C17.1, U1.1 (CPO)
unnamed: C18.2, U1.3 (VCP)
unnamed: C12.2, U2.2 (CPI)
unnamed: C12.1, U2.1 (CPO)
unnamed: C13.2, U2.3 (VCP)
VBUS: C2.1, C3.1, C4.1, C13.1, C14.1, C15.1, C16.1, C18.1, J1.1, U1.4 (VS), U1.11 (VS), U2.4 (VS), U2.11 (VS)

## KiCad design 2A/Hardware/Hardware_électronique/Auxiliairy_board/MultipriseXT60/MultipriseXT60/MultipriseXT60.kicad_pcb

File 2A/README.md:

# CDF-2025
Github de la Coupe de France de Robotique!

#REGLEMENTS
https://www.coupederobotique.fr/accueil/le-concours/reglement-2025/
https://www.coupederobotique.fr/wp-content/uploads/Eurobot2025_Rules.pdf

#DIAPO 
[https://enseafr-my.sharepoint.com/:p:/g/personal/antoine_lemarignier_ensea_fr/Eb2eWKZeK-NNrEKdino8REcB281sSVFofJ1WQgk0IBzqbg?e=ZdGJZ5](https://enseafr-my.sharepoint.com/:p:/g/personal/antoine_lemarignier_ensea_fr/ESafam9fs7ZCg727WFCmVboB-b12O3MPg7kT_spCKCZYLA?e=d9OOJI)

## Photo Robot :

## Liste des participants :
- Lorenzo ROMEO
- Antoine LEMARIGNER
- Mateo GOMES
- Nathan BAINARD
- Ewan ZAHRA-THENAULT
- Khalid ZOUHAIR
- Abderhamane EL FELSOUFI 
- Mohamed EL KOURMISS 
- Sammy GROS
- Matis GARBEZ
- Kenny SAINT FLEUR

## Partenaires :
- [x] Wurth
- [x] Elsys Design
- [x] RS
- [x] Acksys

# Etat du Projet 

## PCB MOTHERBOARD : 
- lien : https://github.com/AresEnsea/2425_Projet2A_AresCFR/edit/main/2A/Hardware/Hardware_%C3%A9lectronique/MainBoard/PCB_test/
- [x] Actuellement en V2
## PCBs auxiliaires :
- [x] steppers https://github.com/AresEnsea/2425_Projet2A_AresCFR/tree/main/2A/Hardware/Hardware_%C3%A9lectronique/Auxiliairy_board/PCB_Stepper
- [x] Moteurs base roulante https://github.com/AresEnsea/2425_Projet2A_AresCFR/new/main/2A/Hardware/Hardware_%C3%A9lectronique/Auxiliairy_board/PCB_Moteur
- [x] Servo moteurs https://github.com/AresEnsea/2425_Projet2A_AresCFR/tree/main/2A/Hardware/Hardware_%C3%A9lectronique/Auxiliairy_board/PCB_Servo

## Méca :
lien modèle 3D : https://cad.onshape.com/documents/e7dd6126290aaac8861c9b96/w/d5c385b6723083ea50ea9e11/e/9022f36f38f961f67dfb7efc?renderMode=0&uiState=66fbe8290d120e0a630e1b35
- [x] Base roulante du robot complète
- [x] Pinces attrape canettes
- [x] Chariots élévateurs
- [x] Banderole
- [x] Fixations PCB
- [ ] Management de cables
- [ ] Odométrie
- [ ] Bouton d'arret d'urgence
- [ ] Tirette de démarrage

## ROS2 embarqué
- lien workspace ros : https://github.com/AresEnsea/2425_Projet2A_AresCFR/tree/main/2A/Firmware/ros2_ws
- [x] Liaison UART pi-STM32
- [x] Rosbags moteurs-actionneurs-Lidar
- [x] Interface écran
- [ ] Odométrie
- lien workspace lidar : https://github.com/AresEnsea/2425_Projet2A_AresCFR/tree/main/2A/Firmware/ydlidar_ros2_ws
- [x] Scan fonctionnel
- [ ] Tout mettre dans le workspace principal

## STM32
lien projet STM32 : https://github.com/AresEnsea/2425_Projet2A_AresCFR/tree/main/2A/Firmware/STM32_moteurs
- [x] V1 code stm32 moteurs réagissant à la pi
- [ ] V2 sur le microprocesseur du PCB

## Vision
lien projet Vision : https://github.com/AresEnsea/2425_Projet2A_AresCFR/tree/main/2A/Vision
- [x] Calibration caméra
- [x] Détection Aruco de la table
- [x] Suivi du mouvement d'un Aruco
- [ ] Transformer les informations de la caméra en carte pour le ROS

## Réseau
- [x] Administration de routeurs
- [x] Ping à travers 2 routeurs
- [x] Avoir un réseau transportable à la Coupe
- [ ] Connecter la pi et la jetson à un même réseau wifi pour communiquer
   
# Répartition par tâche :

## 1-ROS2/STM32 :
- Antoine
- Mateo
- Sammy

Le compte rendu de notre équipe sur le software embarqué se trouve dans le ReadMe.md du dossier Firmware :
https://github.com/AresEnsea/2425_Projet2A_AresCFR/blob/main/2A/Firmware/README.md

## 2-Traitement Image :
- Khalid
- Mohamed
- Abderahmane

Le compte rendu de notre équipe sur le traitement d'image est présent ici :
https://github.com/AresEnsea/2425_Projet2A_AresCFR/blob/main/2A/Vision/README.md

## 3-PCB :
- Kenny
- Ewan

Le compte rendu de notre équipe sur le PCB est présent ici :
https://github.com/AresEnsea/2425_Projet2A_AresCFR/tree/main/2A/Hardware/Hardware_électronique/readme.md

## 4-Mécanique :
- Lorenzo
- Matis
  
Le compte rendu pour la partie mécanique est disponible ici :
https://github.com/AresEnsea/2425_Projet2A_AresCFR/tree/main/2A/Hardware/Hardware_Mécanique/README.md

## 5-Réseau :
- Nathan
  
Le compte rendu pour la partie réseau est disponible ici :
https://github.com/AresEnsea/2425_Projet2A_AresCFR/tree/main/2A/Reseau/README.md

## 6-Planification :
- Mateo
- Antoine

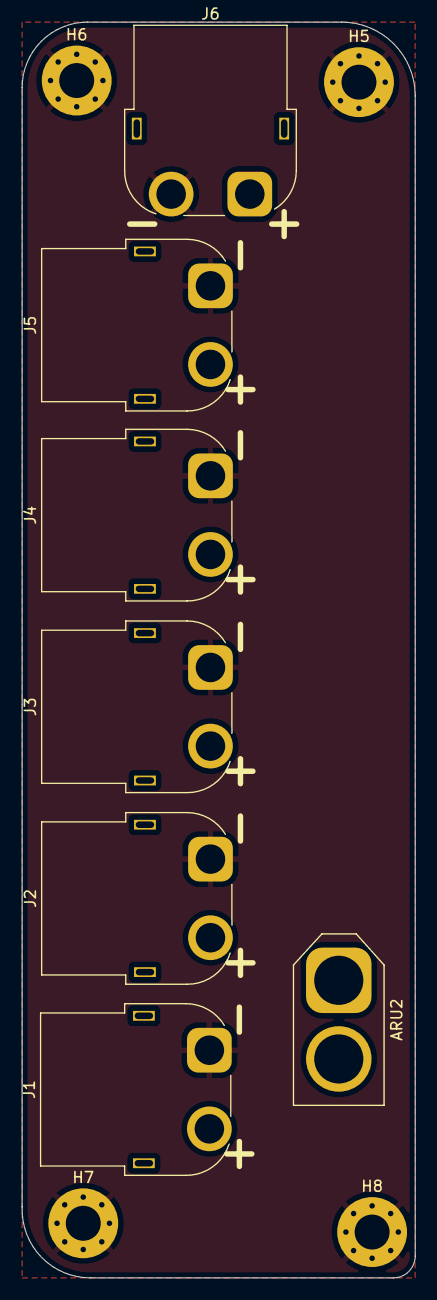
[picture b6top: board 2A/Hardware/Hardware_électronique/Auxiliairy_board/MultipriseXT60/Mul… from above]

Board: 2 copper layers, 36.0 x 115.0 mm, 11 parts (0 on the bottom side), 3 nets, no tracks yet.

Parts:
ARU2: 180G-2; AMASS_XT60-F_1x02_P7.20mm_Vertical
H5, H6, H7, H8: MountingHole_Pad; MountingHole_3.2mm_M3_Pad_Via
J1: Moteur_gauche; AMASS_XT60PW-F_1x02_P7.20mm_Horizontal
J2: Moteur_Droit; AMASS_XT60PW-F_1x02_P7.20mm_Horizontal
J3: Sécurité; AMASS_XT60PW-F_1x02_P7.20mm_Horizontal
J4: Mainboard; AMASS_XT60PW-F_1x02_P7.20mm_Horizontal
J5: Routeur; AMASS_XT60PW-F_1x02_P7.20mm_Horizontal
J6: Batteries; AMASS_XT60PW-F_1x02_P7.20mm_Horizontal

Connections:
BAT+: ARU2.1, J3.2, J4.2, J5.2, J6.1
GND: H5.1, H6.1, H7.1, H8.1, J1.1, J2.1, J3.1, J4.1, J5.1, J6.2
SEC: ARU2.2, J1.2, J2.2
